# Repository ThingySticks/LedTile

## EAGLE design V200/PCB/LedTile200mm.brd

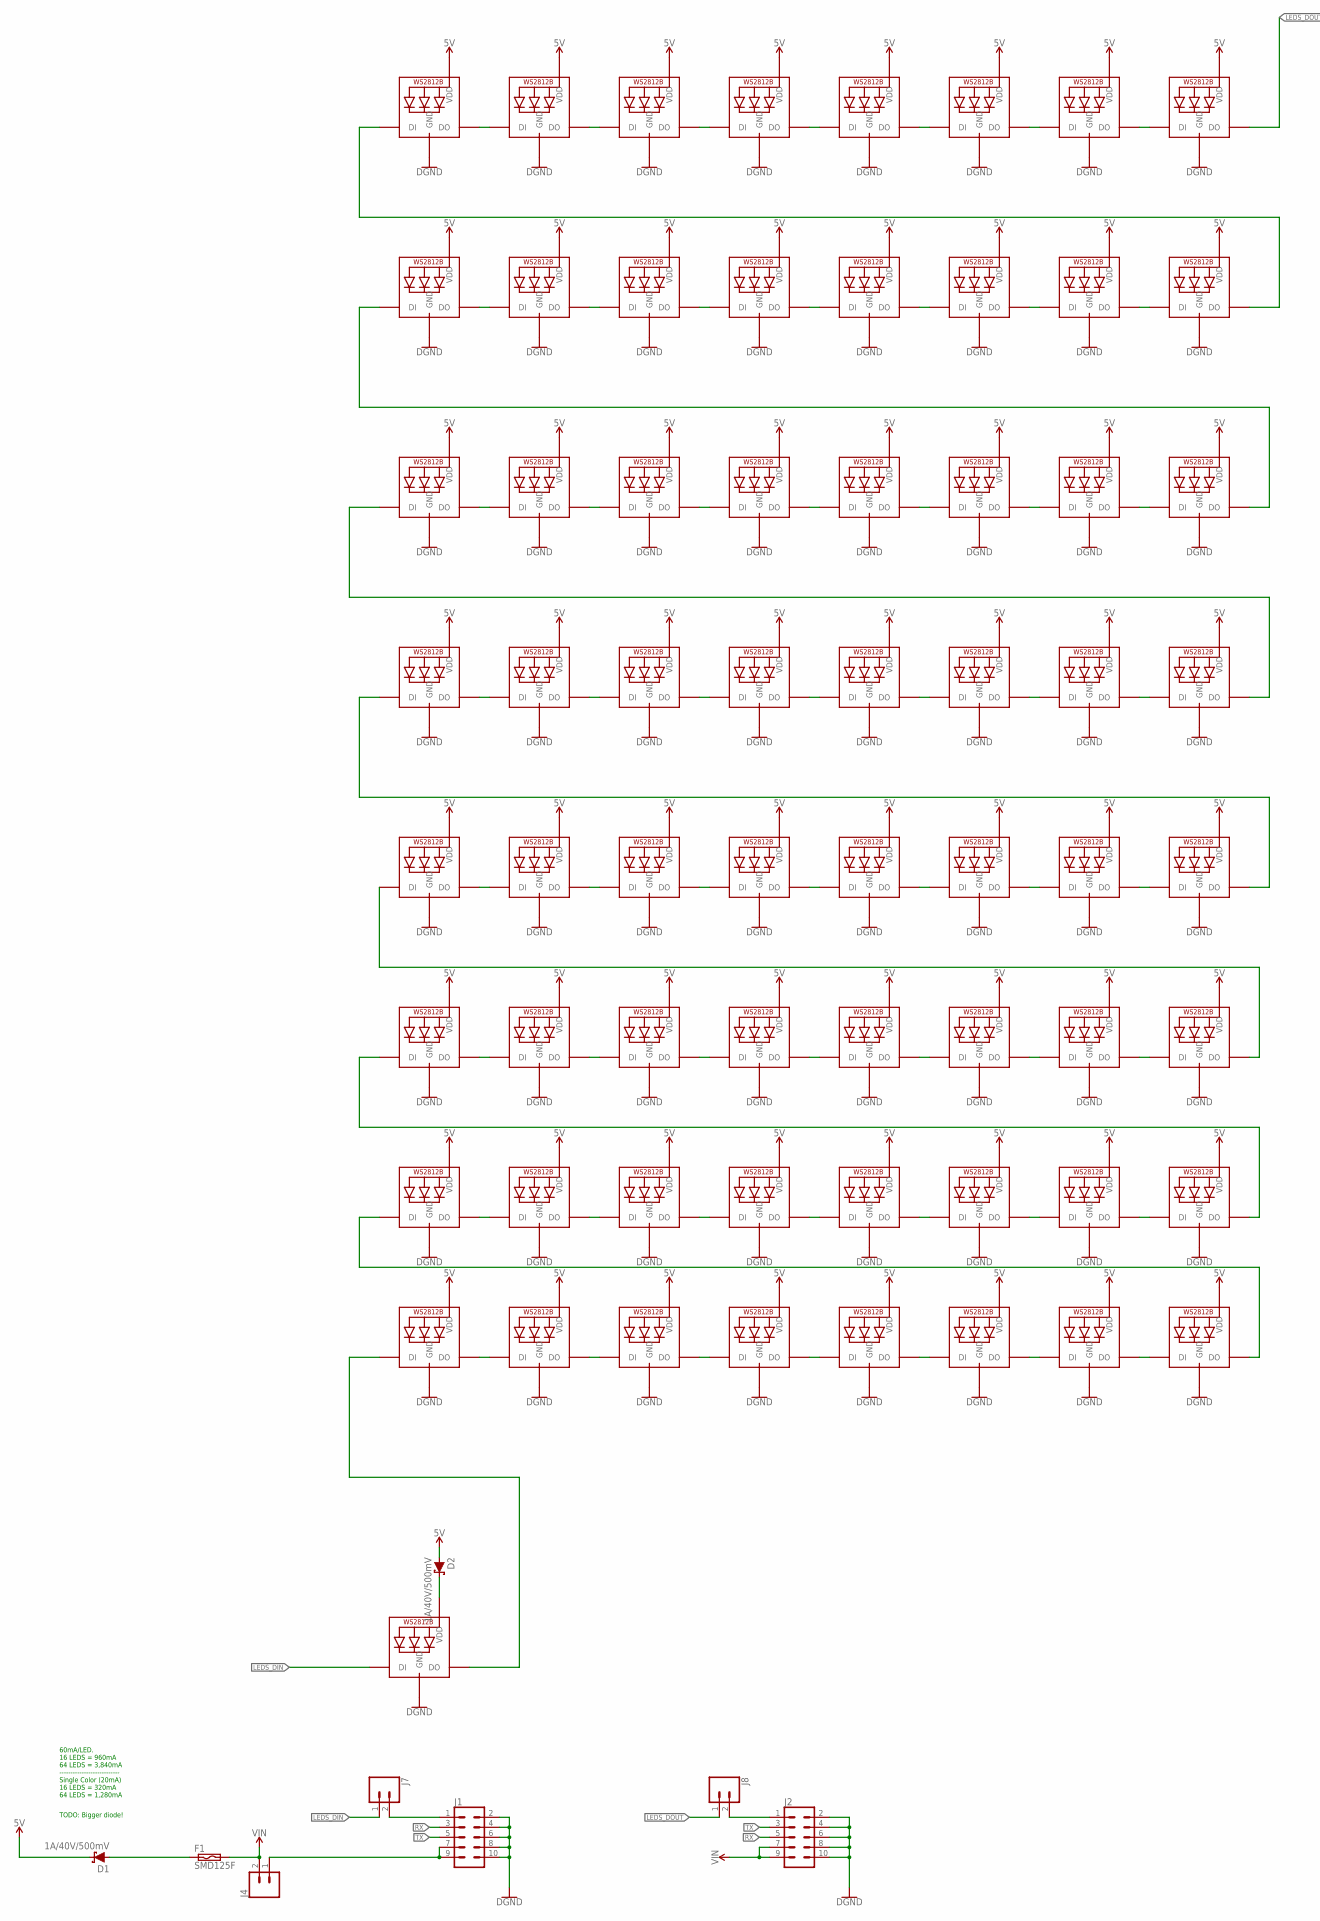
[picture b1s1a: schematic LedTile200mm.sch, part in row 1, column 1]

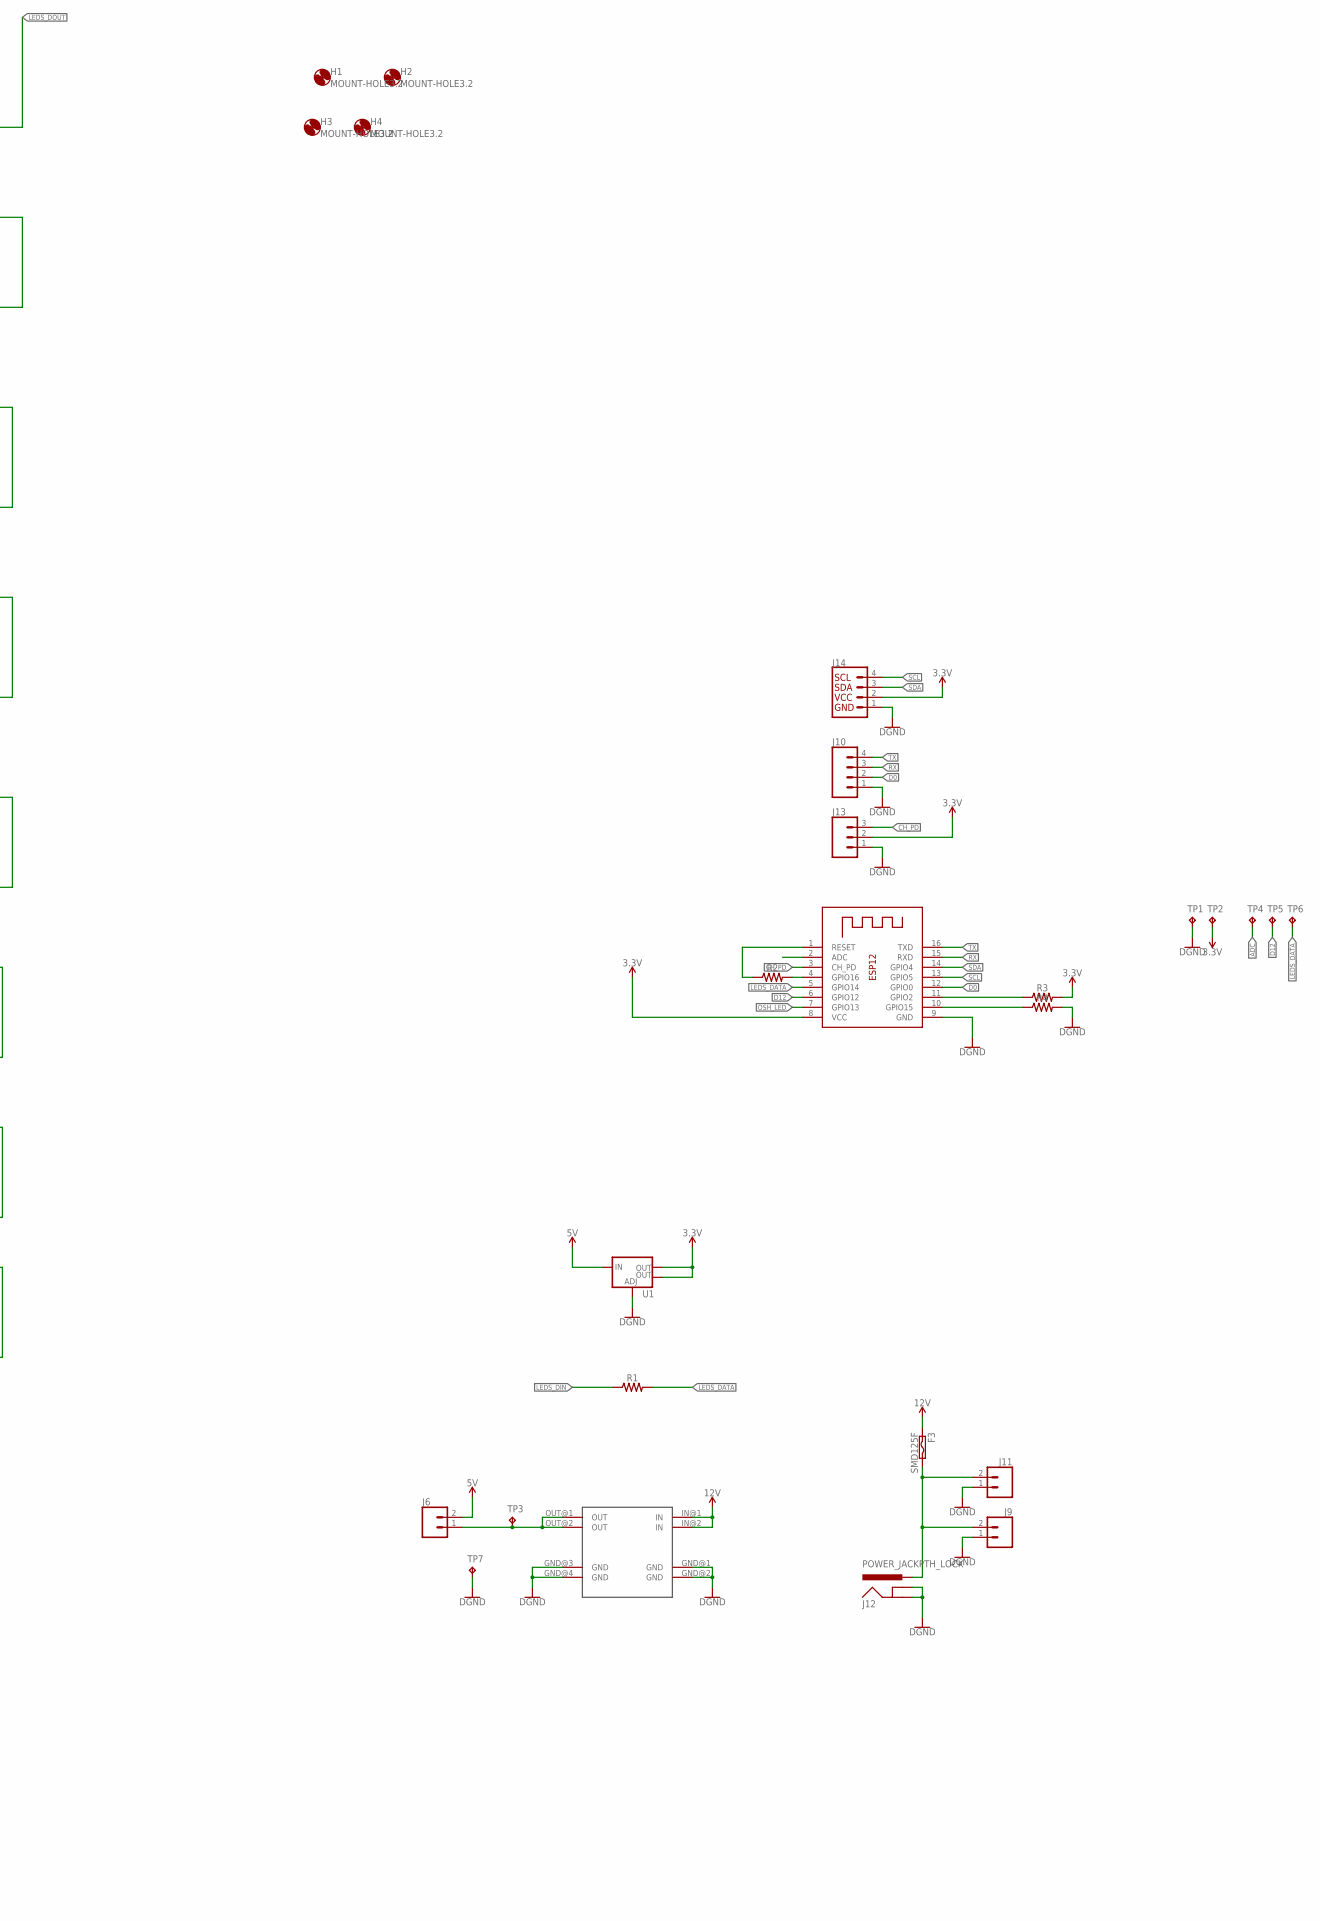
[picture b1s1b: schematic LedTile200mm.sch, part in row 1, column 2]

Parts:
D1, D2: 1A/40V/500mV; SMA-DIODE
F1, F3: SMD125F; SMD050F
H1, H2, H3, H4: MOUNT-HOLE3.2; 3,2
J1, J2: CONN_05X2RA; 2X5-RA
J4, J6, J7, J8: CONN_02; 1X02
J9, J11: CONN_025MM; SCREWTERMINAL-5MM-2
J10: CONN_04; 1X04
J12: POWER_JACKPTH_LOCK; POWER_JACK_PTH_LOCK
J13: CONN_03; 1X03
J14: I2C_STANDARD; 1X04
LED1, LED2, LED3, LED4, LED5, LED6, LED7, LED8, LED9, LED10, LED11, LED12, LED13, LED14, LED15, LED16, LED17, LED18, LED19, LED20, LED21, LED22, LED23, LED24, LED25, LED26, LED27, LED28, LED29, LED30, LED31, LED32, LED33, LED34, LED35, LED36, LED37, LED38, LED39, LED40, LED41, LED42, LED43, LED44, LED45, LED46, LED47, LED48, LED49, LED50, LED51, LED52, LED53, LED54, LED55, LED56, LED57, LED58, LED59, LED60, LED61, LED62, LED63, LED64, LED65: WS2812B5050; WS2812B
R1, R2, R3, R4: 0805
TP1, TP2, TP3, TP4, TP5, TP6, TP7: TPTP16R; TP16R
U1: V_REG_LM1117SOT223; SOT223
U$1: MINI-BUCK-MODULE-3A
X1: ESP-12

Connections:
3.3V: J13.2, J14.2, R3.2, TP2.TP, U1.2 (OUT), U1.4 (OUT), X1.8 (VCC)
5V: D1.C, D2.A, J6.2, LED1.1-VDD (VDD), LED2.1-VDD (VDD), LED3.1-VDD (VDD), LED4.1-VDD (VDD), LED5.1-VDD (VDD), LED6.1-VDD (VDD), LED7.1-VDD (VDD), LED8.1-VDD (VDD), LED9.1-VDD (VDD), LED10.1-VDD (VDD), LED11.1-VDD (VDD), LED12.1-VDD (VDD), LED13.1-VDD (VDD), LED14.1-VDD (VDD), LED15.1-VDD (VDD), LED16.1-VDD (VDD), LED17.1-VDD (VDD), LED18.1-VDD (VDD), LED19.1-VDD (VDD), LED20.1-VDD (VDD), LED21.1-VDD (VDD), LED22.1-VDD (VDD), LED23.1-VDD (VDD), LED24.1-VDD (VDD), LED25.1-VDD (VDD), LED26.1-VDD (VDD), LED27.1-VDD (VDD), LED28.1-VDD (VDD), LED29.1-VDD (VDD), LED30.1-VDD (VDD), LED31.1-VDD (VDD), LED32.1-VDD (VDD), LED33.1-VDD (VDD), LED34.1-VDD (VDD), LED35.1-VDD (VDD), LED36.1-VDD (VDD), LED37.1-VDD (VDD), LED38.1-VDD (VDD), LED39.1-VDD (VDD), LED40.1-VDD (VDD), LED41.1-VDD (VDD), LED42.1-VDD (VDD), LED43.1-VDD (VDD), LED44.1-VDD (VDD), LED45.1-VDD (VDD), LED46.1-VDD (VDD), LED47.1-VDD (VDD), LED48.1-VDD (VDD), LED49.1-VDD (VDD), LED50.1-VDD (VDD), LED51.1-VDD (VDD), LED52.1-VDD (VDD), LED53.1-VDD (VDD), LED54.1-VDD (VDD), LED55.1-VDD (VDD), LED56.1-VDD (VDD), LED57.1-VDD (VDD), LED58.1-VDD (VDD), LED59.1-VDD (VDD), LED60.1-VDD (VDD), LED61.1-VDD (VDD), LED62.1-VDD (VDD), LED63.1-VDD (VDD), LED64.1-VDD (VDD), U1.3 (IN)
12V: F3.1, U$1.IN@1 (IN), U$1.IN@2 (IN)
ADC: TP4.TP, X1.2 (ADC)
CH_PD: J13.3, X1.3 (CH_PD)
D0: J10.2, X1.12 (GPIO0)
D12: TP5.TP, X1.6 (GPIO12)
GND: J1.2, J1.4, J1.6, J1.8, J1.10, J2.2, J2.4, J2.6, J2.8, J2.10, J9.1, J10.1, J11.1, J12.GND, J12.GNDBREAK, J13.1, J14.1, LED1.3-GND (GND), LED2.3-GND (GND), LED3.3-GND (GND), LED4.3-GND (GND), LED5.3-GND (GND), LED6.3-GND (GND), LED7.3-GND (GND), LED8.3-GND (GND), LED9.3-GND (GND), LED10.3-GND (GND), LED11.3-GND (GND), LED12.3-GND (GND), LED13.3-GND (GND), LED14.3-GND (GND), LED15.3-GND (GND), LED16.3-GND (GND), LED17.3-GND (GND), LED18.3-GND (GND), LED19.3-GND (GND), LED20.3-GND (GND), LED21.3-GND (GND), LED22.3-GND (GND), LED23.3-GND (GND), LED24.3-GND (GND), LED25.3-GND (GND), LED26.3-GND (GND), LED27.3-GND (GND), LED28.3-GND (GND), LED29.3-GND (GND), LED30.3-GND (GND), LED31.3-GND (GND), LED32.3-GND (GND), LED33.3-GND (GND), LED34.3-GND (GND), LED35.3-GND (GND), LED36.3-GND (GND), LED37.3-GND (GND), LED38.3-GND (GND), LED39.3-GND (GND), LED40.3-GND (GND), LED41.3-GND (GND), LED42.3-GND (GND), LED43.3-GND (GND), LED44.3-GND (GND), LED45.3-GND (GND), LED46.3-GND (GND), LED47.3-GND (GND), LED48.3-GND (GND), LED49.3-GND (GND), LED50.3-GND (GND), LED51.3-GND (GND), LED52.3-GND (GND), LED53.3-GND (GND), LED54.3-GND (GND), LED55.3-GND (GND), LED56.3-GND (GND), LED57.3-GND (GND), LED58.3-GND (GND), LED59.3-GND (GND), LED60.3-GND (GND), LED61.3-GND (GND), LED62.3-GND (GND), LED63.3-GND (GND), LED64.3-GND (GND), LED65.3-GND (GND), R4.2, TP1.TP, TP7.TP, U1.1 (ADJ), U$1.GND@1 (GND), U$1.GND@2 (GND), U$1.GND@3 (GND), U$1.GND@4 (GND), X1.9 (GND)
LEDS_DATA: R1.2, TP6.TP, X1.5 (GPIO14)
LEDS_DIN: J7.1, LED65.4-DIN (DI), R1.1
LEDS_DOUT: J8.1, LED64.2-DOUT (DO)
unnamed: LED1.2-DOUT (DO), LED2.4-DIN (DI)
unnamed: LED2.2-DOUT (DO), LED3.4-DIN (DI)
unnamed: LED3.2-DOUT (DO), LED4.4-DIN (DI)
unnamed: LED4.2-DOUT (DO), LED5.4-DIN (DI)
unnamed: LED5.2-DOUT (DO), LED6.4-DIN (DI)
unnamed: LED6.2-DOUT (DO), LED7.4-DIN (DI)
unnamed: LED7.2-DOUT (DO), LED8.4-DIN (DI)
unnamed: LED8.2-DOUT (DO), LED9.4-DIN (DI)
unnamed: LED1.4-DIN (DI), LED65.2-DOUT (DO)
unnamed: R3.1, X1.11 (GPIO2)
unnamed: R4.1, X1.10 (GPIO15)
unnamed: R2.1, X1.1 (RESET)
unnamed: R2.2, X1.4 (GPIO16)
unnamed: J6.1, TP3.TP, U$1.OUT@1 (OUT), U$1.OUT@2 (OUT)
unnamed: LED9.2-DOUT (DO), LED10.4-DIN (DI)
unnamed: LED10.2-DOUT (DO), LED11.4-DIN (DI)
unnamed: LED11.2-DOUT (DO), LED12.4-DIN (DI)
unnamed: LED12.2-DOUT (DO), LED13.4-DIN (DI)
unnamed: LED13.2-DOUT (DO), LED14.4-DIN (DI)
unnamed: LED14.2-DOUT (DO), LED15.4-DIN (DI)
unnamed: LED15.2-DOUT (DO), LED16.4-DIN (DI)
unnamed: LED16.2-DOUT (DO), LED17.4-DIN (DI)
unnamed: LED17.2-DOUT (DO), LED18.4-DIN (DI)
unnamed: LED18.2-DOUT (DO), LED19.4-DIN (DI)
unnamed: LED19.2-DOUT (DO), LED20.4-DIN (DI)
unnamed: LED20.2-DOUT (DO), LED21.4-DIN (DI)
unnamed: LED21.2-DOUT (DO), LED22.4-DIN (DI)
unnamed: LED22.2-DOUT (DO), LED23.4-DIN (DI)
unnamed: LED23.2-DOUT (DO), LED24.4-DIN (DI)
unnamed: LED24.2-DOUT (DO), LED25.4-DIN (DI)
unnamed: LED25.2-DOUT (DO), LED26.4-DIN (DI)
unnamed: LED26.2-DOUT (DO), LED27.4-DIN (DI)
unnamed: LED27.2-DOUT (DO), LED28.4-DIN (DI)
unnamed: LED28.2-DOUT (DO), LED29.4-DIN (DI)
unnamed: LED29.2-DOUT (DO), LED30.4-DIN (DI)
unnamed: LED30.2-DOUT (DO), LED31.4-DIN (DI)
unnamed: LED31.2-DOUT (DO), LED32.4-DIN (DI)
unnamed: LED32.2-DOUT (DO), LED33.4-DIN (DI)
unnamed: LED33.2-DOUT (DO), LED34.4-DIN (DI)
unnamed: LED34.2-DOUT (DO), LED35.4-DIN (DI)
unnamed: LED35.2-DOUT (DO), LED36.4-DIN (DI)
unnamed: LED36.2-DOUT (DO), LED37.4-DIN (DI)
unnamed: LED37.2-DOUT (DO), LED38.4-DIN (DI)
unnamed: LED38.2-DOUT (DO), LED39.4-DIN (DI)
unnamed: LED39.2-DOUT (DO), LED40.4-DIN (DI)
unnamed: LED40.2-DOUT (DO), LED41.4-DIN (DI)
unnamed: LED41.2-DOUT (DO), LED42.4-DIN (DI)
unnamed: LED42.2-DOUT (DO), LED43.4-DIN (DI)
unnamed: LED43.2-DOUT (DO), LED44.4-DIN (DI)
unnamed: LED44.2-DOUT (DO), LED45.4-DIN (DI)
unnamed: LED45.2-DOUT (DO), LED46.4-DIN (DI)
unnamed: LED46.2-DOUT (DO), LED47.4-DIN (DI)
unnamed: LED47.2-DOUT (DO), LED48.4-DIN (DI)
unnamed: LED48.2-DOUT (DO), LED49.4-DIN (DI)
unnamed: LED49.2-DOUT (DO), LED50.4-DIN (DI)
unnamed: LED50.2-DOUT (DO), LED51.4-DIN (DI)
unnamed: LED51.2-DOUT (DO), LED52.4-DIN (DI)
unnamed: LED52.2-DOUT (DO), LED53.4-DIN (DI)
unnamed: LED53.2-DOUT (DO), LED54.4-DIN (DI)
unnamed: LED54.2-DOUT (DO), LED55.4-DIN (DI)
unnamed: LED55.2-DOUT (DO), LED56.4-DIN (DI)
unnamed: LED56.2-DOUT (DO), LED57.4-DIN (DI)
unnamed: LED57.2-DOUT (DO), LED58.4-DIN (DI)
unnamed: LED58.2-DOUT (DO), LED59.4-DIN (DI)
unnamed: LED59.2-DOUT (DO), LED60.4-DIN (DI)
unnamed: LED60.2-DOUT (DO), LED61.4-DIN (DI)
unnamed: LED61.2-DOUT (DO), LED62.4-DIN (DI)
unnamed: LED62.2-DOUT (DO), LED63.4-DIN (DI)
unnamed: LED63.2-DOUT (DO), LED64.4-DIN (DI)
unnamed: F3.2, J9.2, J11.2, J12.PWR
unnamed: D1.A, F1.1
unnamed: D2.C, LED65.1-VDD (VDD)
unnamed: J2.1, J8.2
unnamed: J1.7, J1.9, J4.1
unnamed: J1.1, J7.2
OSH_LED: X1.7 (GPIO13)
RX: J1.3, J2.5, J10.3, X1.15 (RXD)
SCL: J14.4, X1.13 (GPIO5)
SDA: J14.3, X1.14 (GPIO4)
TX: J1.5, J2.3, J10.4, X1.16 (TXD)
VIN: F1.2, J2.7, J2.9, J4.2

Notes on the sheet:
TODO: Bigger diode!
60mA/LED. 16 LEDS = 960mA 64 LEDS = 3,840mA --------------------------- Single Color (20mA) 16 LEDS = 320mA 64 LEDS = 1,280mA

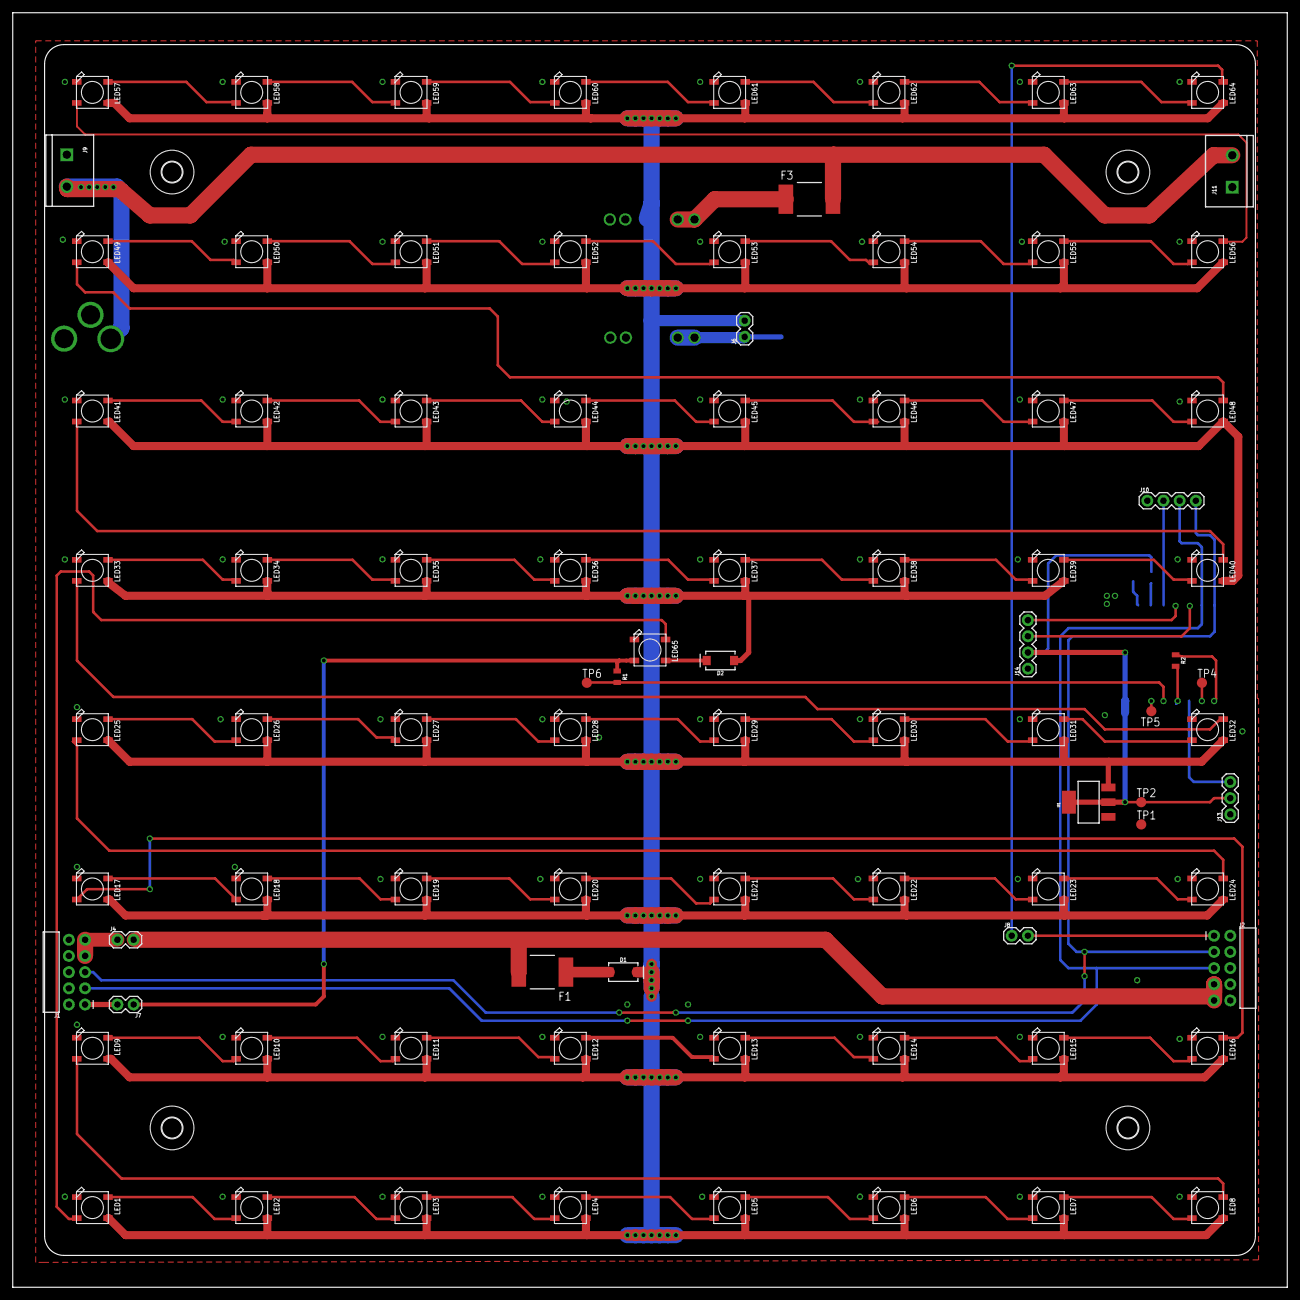
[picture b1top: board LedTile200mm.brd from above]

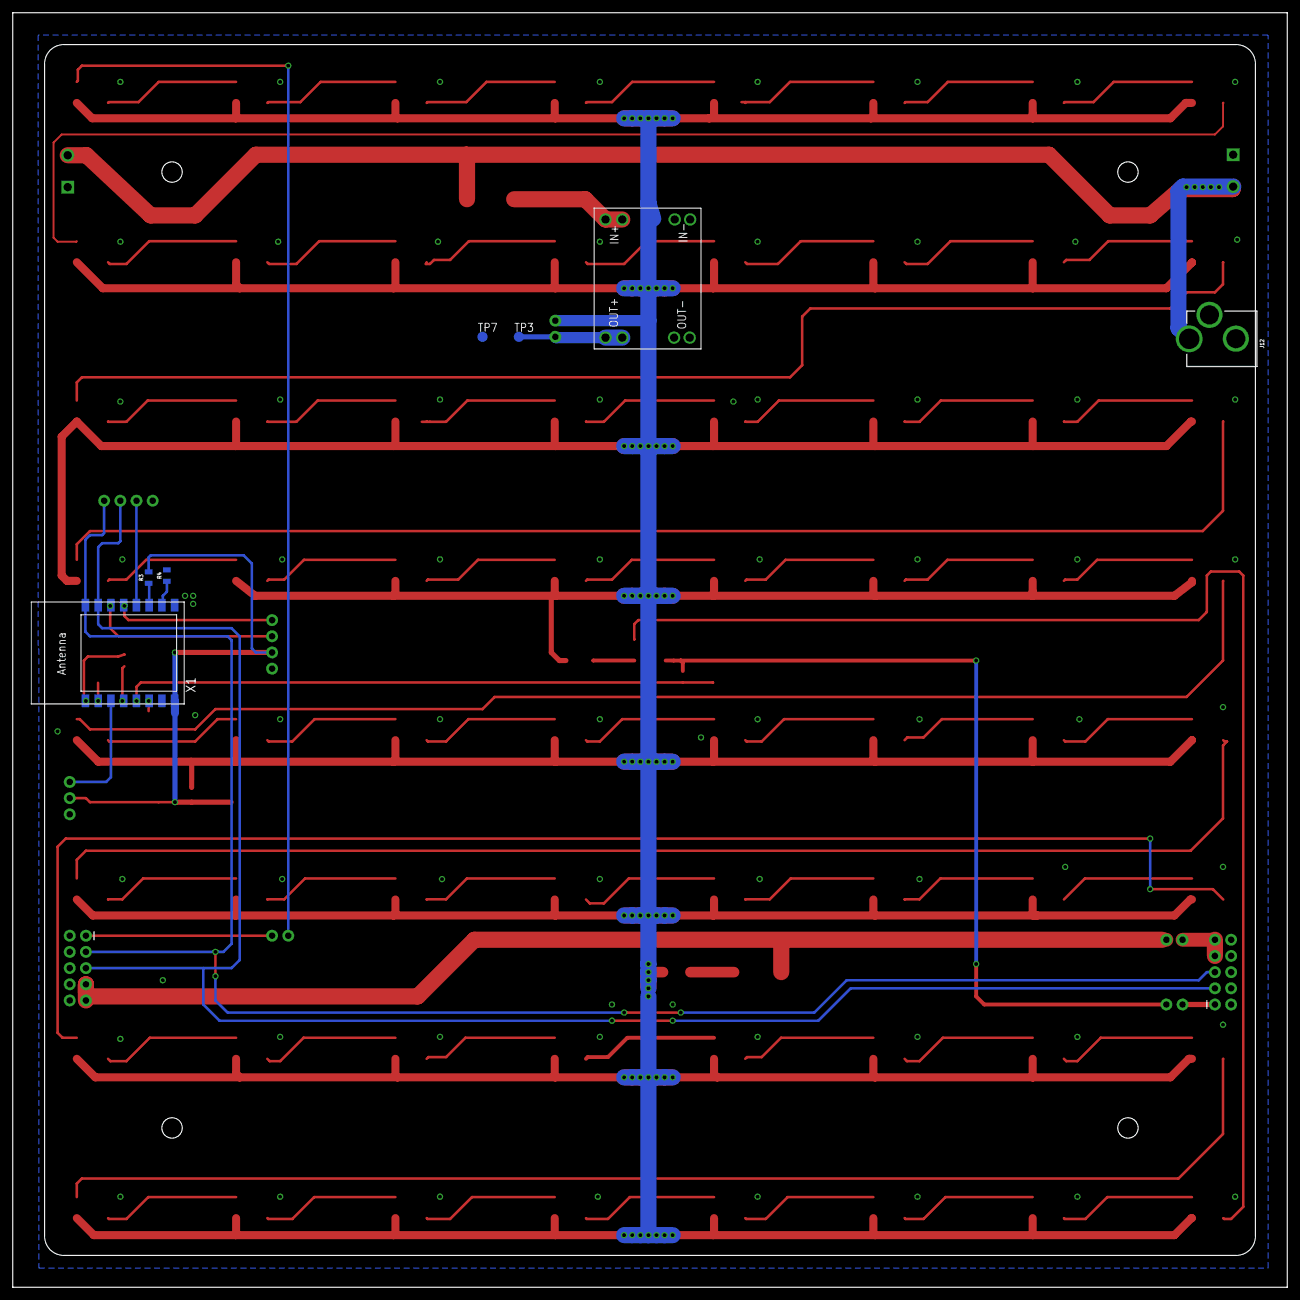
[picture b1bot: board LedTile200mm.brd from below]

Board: 2 copper layers, 200.0 x 200.0 mm, 99 parts (7 on the bottom side), 91 nets.

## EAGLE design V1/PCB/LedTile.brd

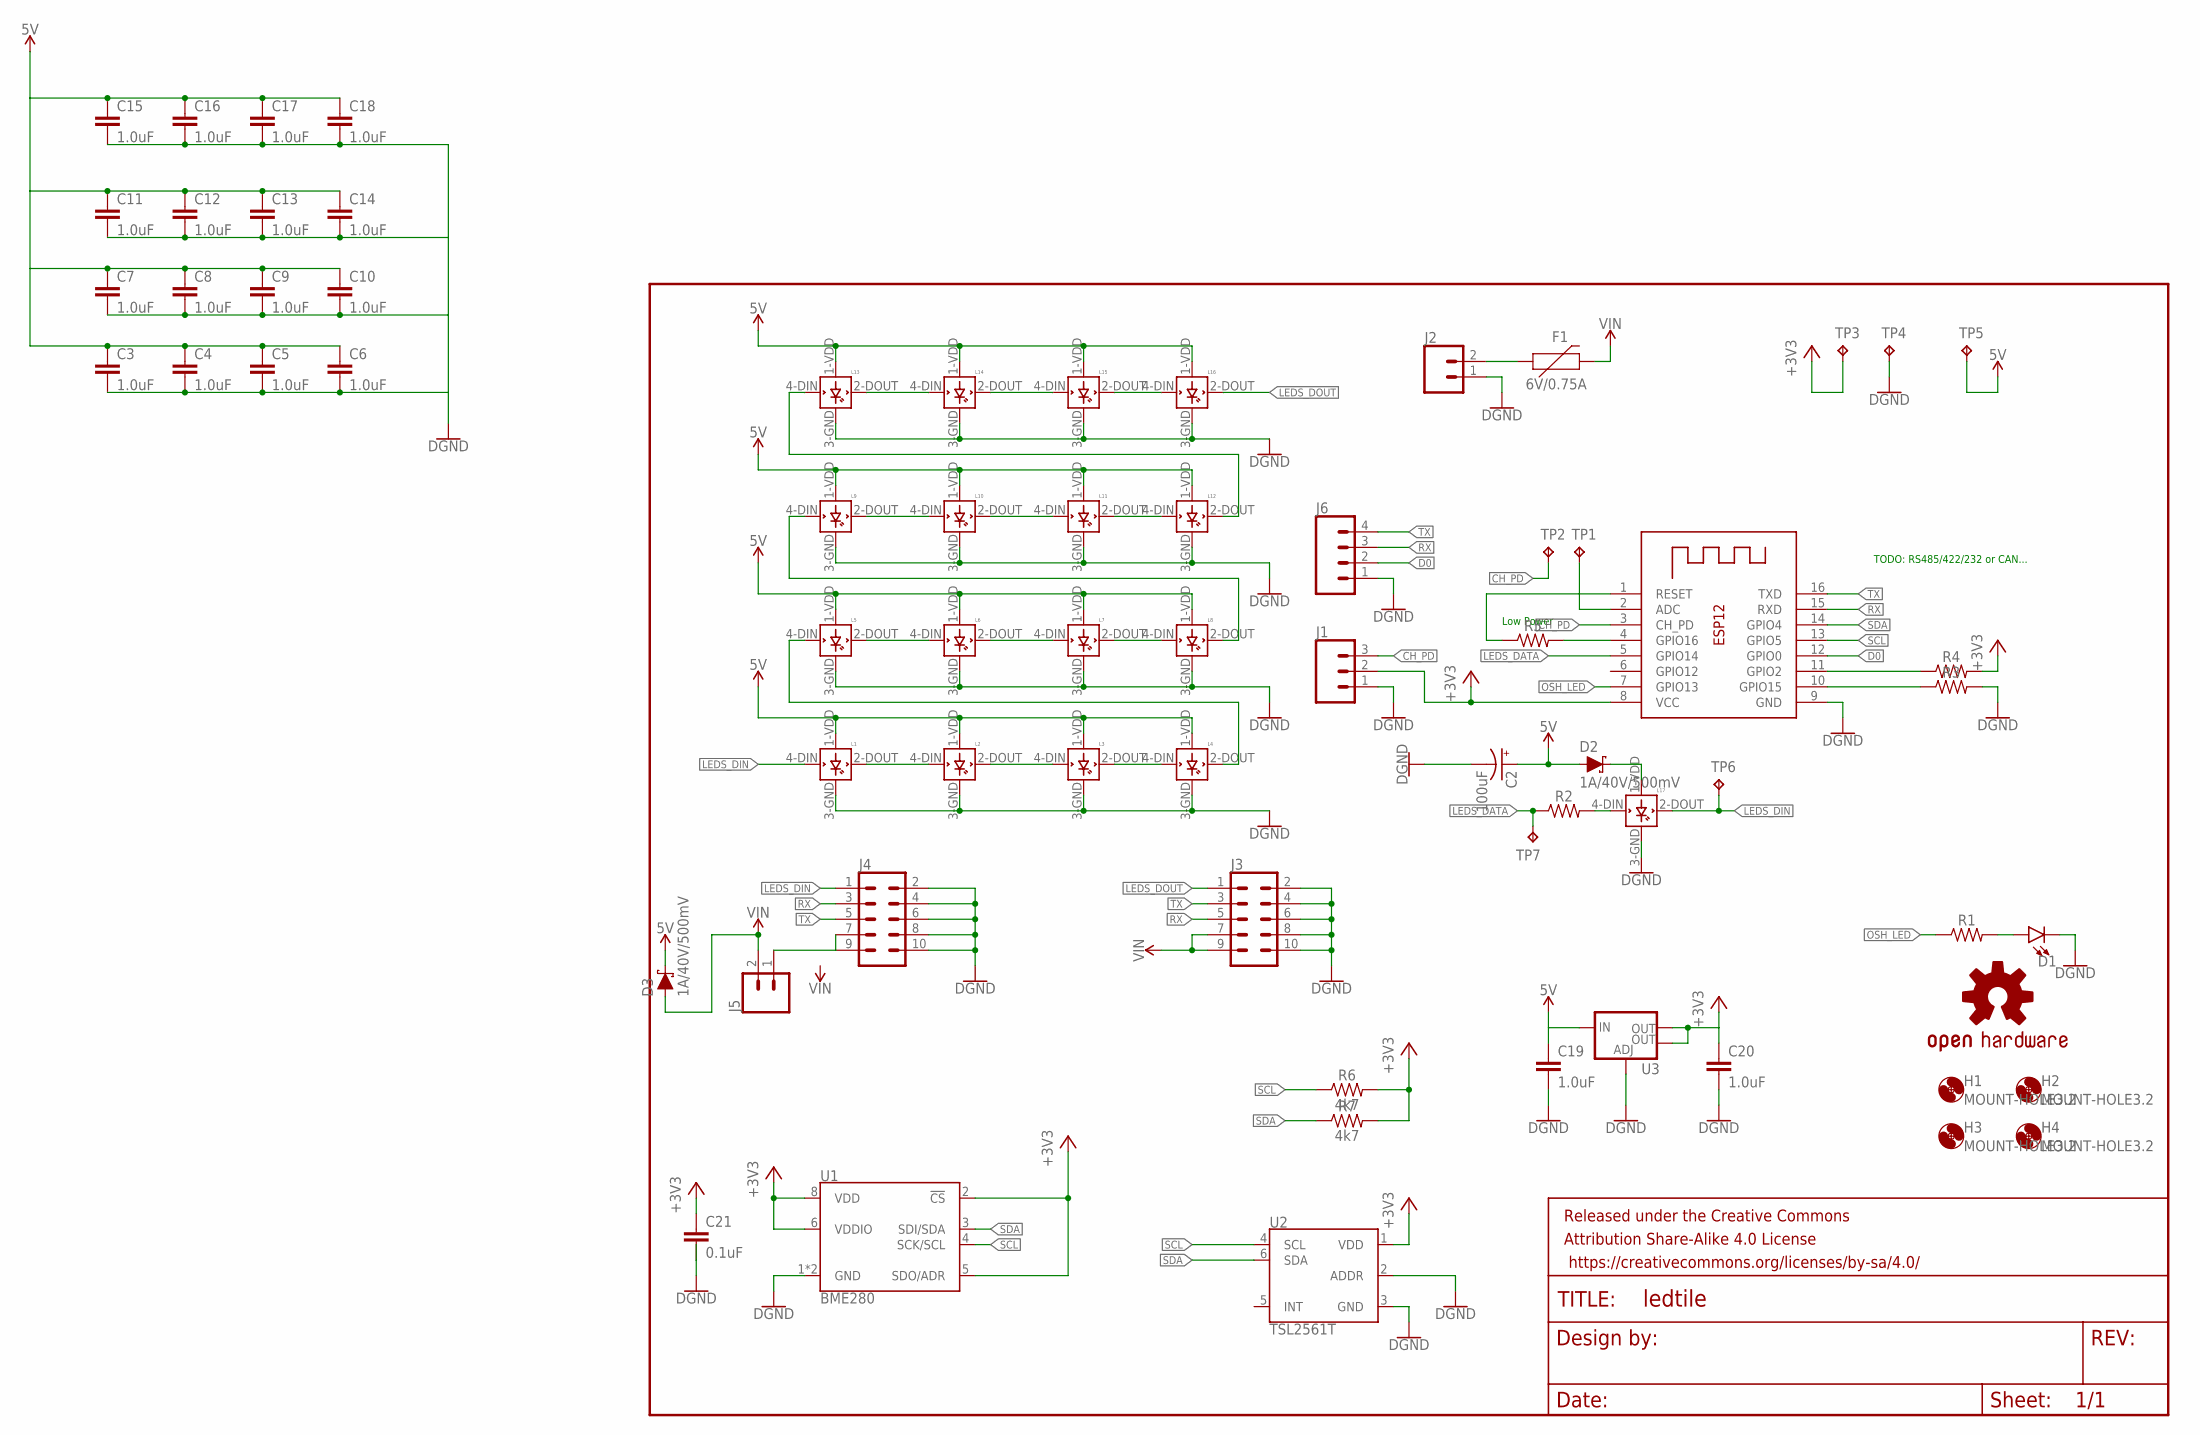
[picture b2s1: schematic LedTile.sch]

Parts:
C2: 100uF; EIA7343
C3, C4, C5, C6, C7, C8, C9, C10, C11, C12, C13, C14, C15, C16, C17, C18, C19, C20: 1.0uF; 0805
C21: 0.1uF; 0805
D1: LED1206-BOTTOM; LED-1206-BOTTOM
D2, D3: 1A/40V/500mV; SMA-DIODE
F1: 6V/0.75A; 1206
FRAME1: FRAME-LETTER; CREATIVE_COMMONS
H1, H2, H3, H4: MOUNT-HOLE3.2; 3,2
J1: CONN_031X03_NO_SILK; 1X03_NO_SILK
J2: CONN_025MM; SCREWTERMINAL-5MM-2
J3, J4: CONN_05X2RA; 2X5-RA
J5: CONN_02; 1X02
J6: CONN_04; 1X04
L1, L2, L3, L4, L5, L6, L7, L8, L9, L10, L11, L12, L13, L14, L15, L16, L17: WS2812B
LOGO1: OSHW-LOGOL; OSHW-LOGO-L
R1, R2, R3, R4, R5: 0805
R6, R7: 4k7; 0805
TP1, TP2, TP3, TP4, TP5, TP6, TP7: TPTP12R; TP12R
U1: BME280; LGA-8-2.5X2.5
U2: TSL2561T; TMB-6
U3: V_REG_LM1117SOT223; SOT223
X1: ESP-12

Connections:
5V: C2.A (+), C3.1, C4.1, C5.1, C6.1, C7.1, C8.1, C9.1, C10.1, C11.1, C12.1, C13.1, C14.1, C15.1, C16.1, C17.1, C18.1, C19.1, D2.A, D3.C, L1.1-VDD (VDD), L2.1-VDD (VDD), L3.1-VDD (VDD), L4.1-VDD (VDD), L5.1-VDD (VDD), L6.1-VDD (VDD), L7.1-VDD (VDD), L8.1-VDD (VDD), L9.1-VDD (VDD), L10.1-VDD (VDD), L11.1-VDD (VDD), L12.1-VDD (VDD), L13.1-VDD (VDD), L14.1-VDD (VDD), L15.1-VDD (VDD), L16.1-VDD (VDD), TP5.TP, U3.3 (IN)
+3V3: C20.1, C21.1, J1.2, R4.2, R6.2, R7.2, TP3.TP, U1.2 (!CS), U1.5 (SDO/ADR), U1.6 (VDDIO), U1.8 (VDD), U2.1 (VDD), U3.2 (OUT), U3.4 (OUT), X1.8 (VCC)
CH_PD: J1.3, TP2.TP, X1.3 (CH_PD)
D0: J6.2, X1.12 (GPIO0)
GND: C2.C (-), C3.2, C4.2, C5.2, C6.2, C7.2, C8.2, C9.2, C10.2, C11.2, C12.2, C13.2, C14.2, C15.2, C16.2, C17.2, C18.2, C19.2, C20.2, C21.2, D1.C, J1.1, J2.1, J3.2, J3.4, J3.6, J3.8, J3.10, J4.2, J4.4, J4.6, J4.8, J4.10, J6.1, L1.3-GND (GND), L2.3-GND (GND), L3.3-GND (GND), L4.3-GND (GND), L5.3-GND (GND), L6.3-GND (GND), L7.3-GND (GND), L8.3-GND (GND), L9.3-GND (GND), L10.3-GND (GND), L11.3-GND (GND), L12.3-GND (GND), L13.3-GND (GND), L14.3-GND (GND), L15.3-GND (GND), L16.3-GND (GND), L17.3-GND (GND), R3.2, TP4.TP, U1.1 (GND), U1.7 (GND), U2.2 (ADDR), U2.3 (GND), U3.1 (ADJ), X1.9 (GND)
LEDS_DATA: R2.1, TP7.TP, X1.5 (GPIO14)
LEDS_DIN: J4.1, L1.4-DIN (DIN), L17.2-DOUT (DOUT), TP6.TP
LEDS_DOUT: J3.1, L16.2-DOUT (DOUT)
unnamed: L1.2-DOUT (DOUT), L2.4-DIN (DIN)
unnamed: L2.2-DOUT (DOUT), L3.4-DIN (DIN)
unnamed: L4.2-DOUT (DOUT), L5.4-DIN (DIN)
unnamed: D2.C, L17.1-VDD (VDD)
unnamed: TP1.TP, X1.2 (ADC)
unnamed: L17.4-DIN (DIN), R2.2
unnamed: L3.2-DOUT (DOUT), L4.4-DIN (DIN)
unnamed: L13.2-DOUT (DOUT), L14.4-DIN (DIN)
unnamed: L14.2-DOUT (DOUT), L15.4-DIN (DIN)
unnamed: L15.2-DOUT (DOUT), L16.4-DIN (DIN)
unnamed: L11.2-DOUT (DOUT), L12.4-DIN (DIN)
unnamed: L12.2-DOUT (DOUT), L13.4-DIN (DIN)
unnamed: L8.2-DOUT (DOUT), L9.4-DIN (DIN)
unnamed: L10.2-DOUT (DOUT), L11.4-DIN (DIN)
unnamed: L9.2-DOUT (DOUT), L10.4-DIN (DIN)
unnamed: L5.2-DOUT (DOUT), L6.4-DIN (DIN)
unnamed: L6.2-DOUT (DOUT), L7.4-DIN (DIN)
unnamed: L7.2-DOUT (DOUT), L8.4-DIN (DIN)
unnamed: R3.1, X1.10 (GPIO15)
unnamed: R4.1, X1.11 (GPIO2)
unnamed: R5.2, X1.4 (GPIO16)
unnamed: R5.1, X1.1 (RESET)
unnamed: D1.A, R1.2
unnamed: J4.7, J4.9, J5.1
unnamed: F1.1, J2.2
OSH_LED: R1.1, X1.7 (GPIO13)
RX: J3.5, J4.3, J6.3, X1.15 (RXD)
SCL: R6.1, U1.4 (SCK/SCL), U2.4 (SCL), X1.13 (GPIO5)
SDA: R7.1, U1.3 (SDI/SDA), U2.6 (SDA), X1.14 (GPIO4)
TX: J3.3, J4.5, J6.4, X1.16 (TXD)
VIN: D3.A, F1.2, J3.7, J3.9, J5.2

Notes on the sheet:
TODO: RS485/422/232 or CAN...
Low Power

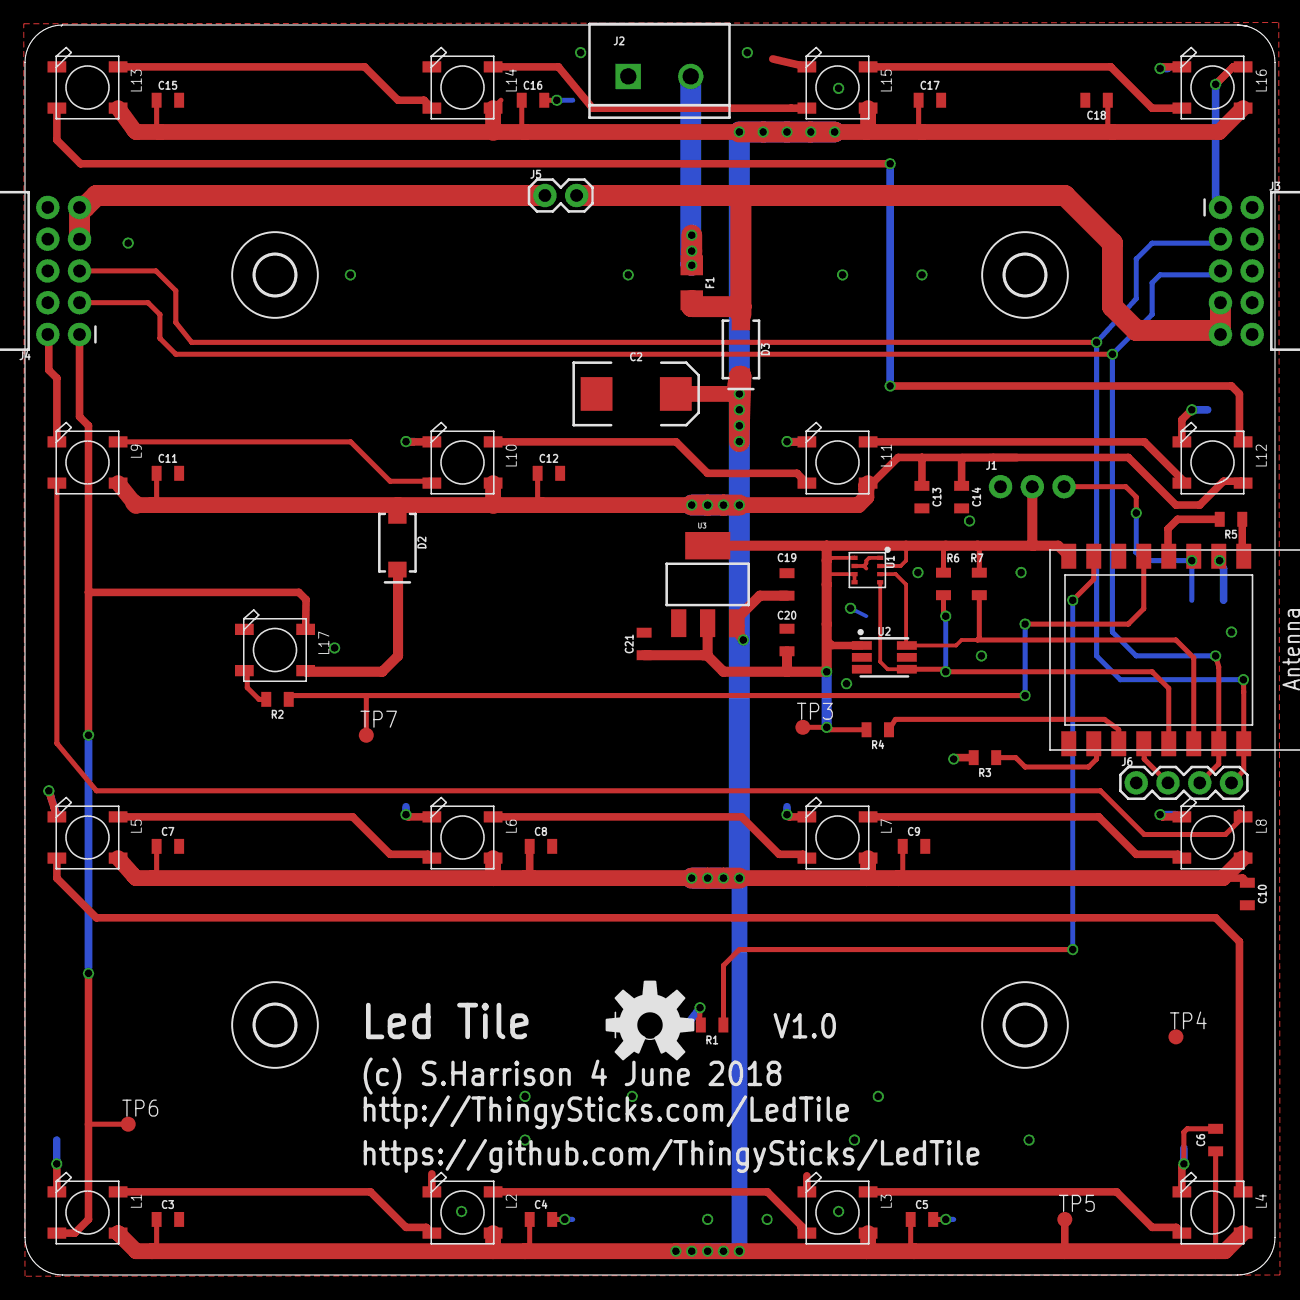
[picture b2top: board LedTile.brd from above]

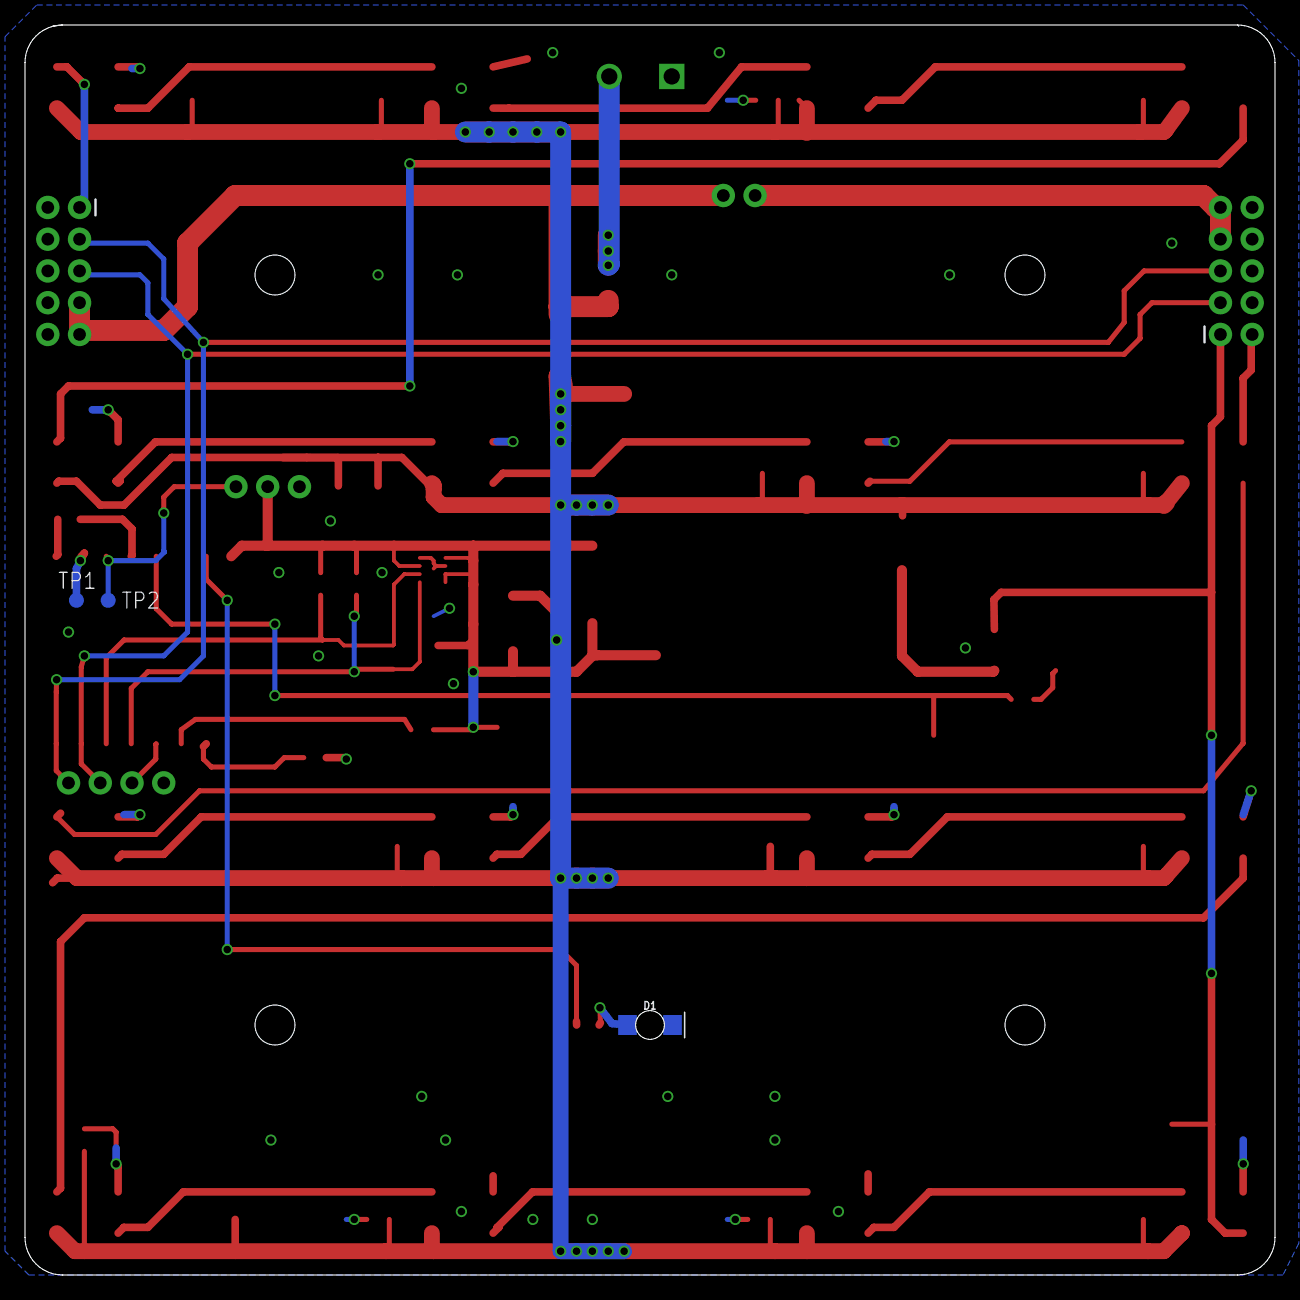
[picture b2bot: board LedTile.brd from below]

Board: 2 copper layers, 100.0 x 100.0 mm, 71 parts (3 on the bottom side), 39 nets.

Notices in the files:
parts and their libraries:
SparkFun-Aesthetics: Licensing: Creative Commons ShareAlike 4.0 International - https://creativecommons.org/licenses/by-sa/4.0
SparkFun-Aesthetics: Released under the Creative Commons Attribution Share-Alike 4.0 License
SparkFun-Aesthetics: https://creativecommons.org/licenses/by-sa/4.0
